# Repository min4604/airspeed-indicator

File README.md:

## Airspeeds system
Can use PC read real time data.

Schematic design end.

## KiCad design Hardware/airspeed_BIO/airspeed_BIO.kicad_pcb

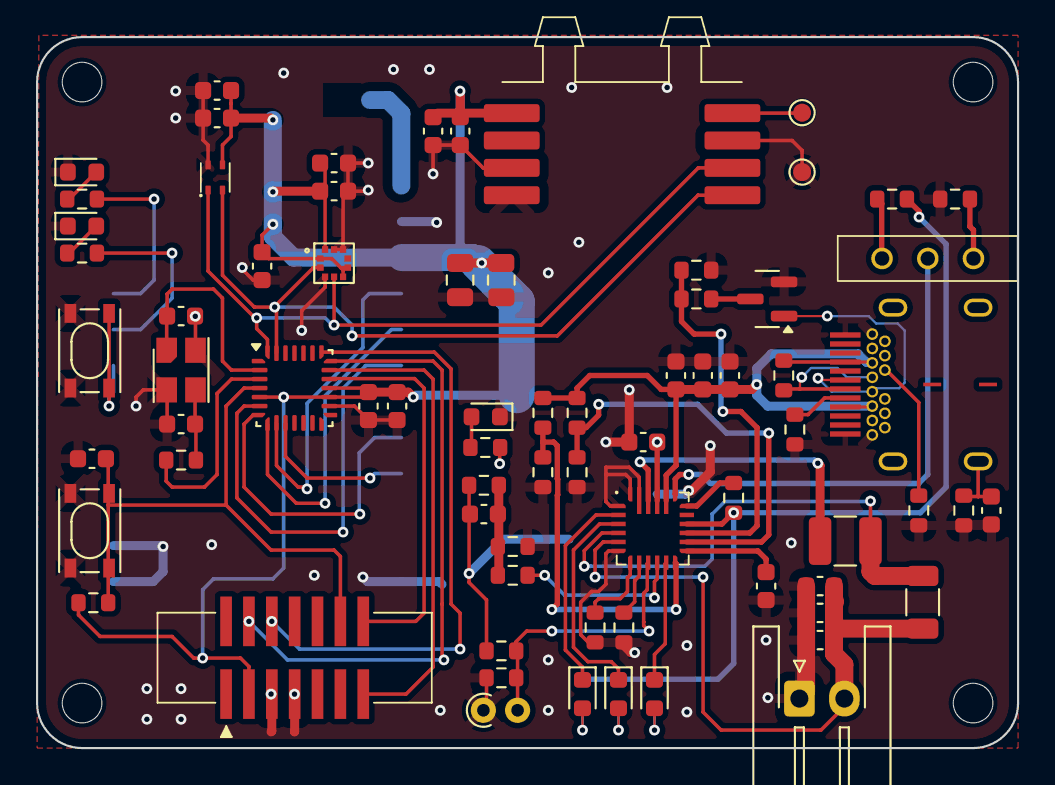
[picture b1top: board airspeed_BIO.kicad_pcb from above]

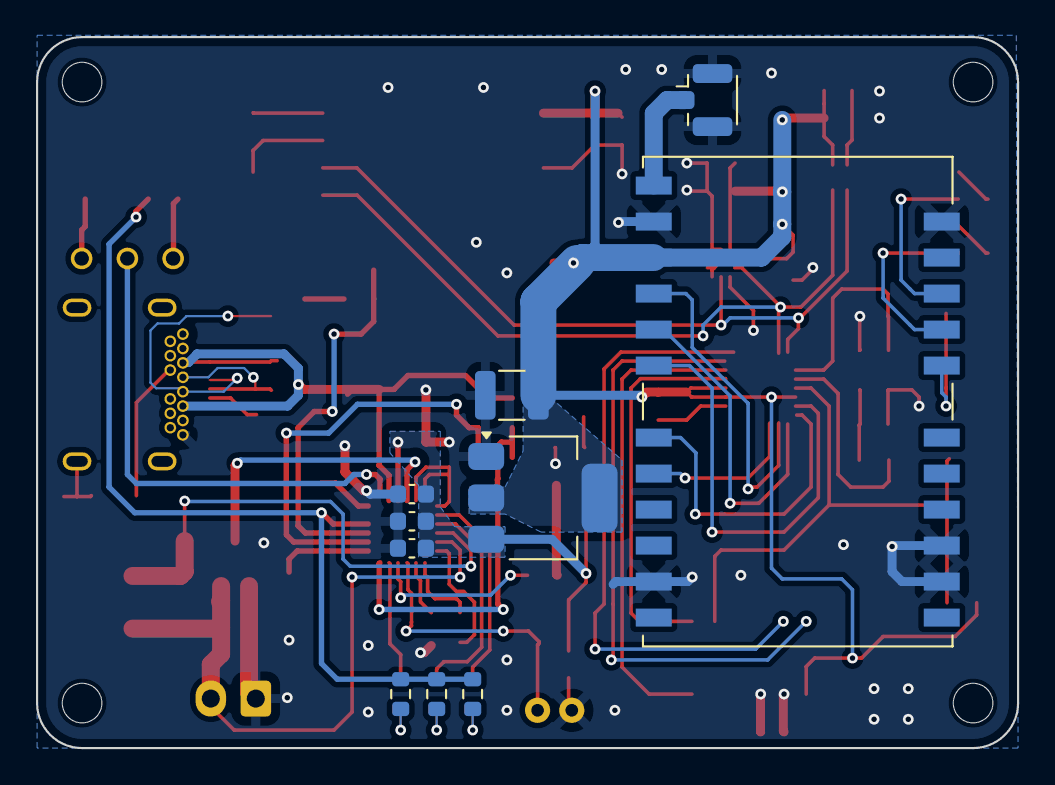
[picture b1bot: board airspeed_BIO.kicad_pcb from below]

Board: 2 copper layers, 54.5 x 39.5 mm, 87 parts (10 on the bottom side), 56 nets.

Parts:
C1, C9, C12: 22uF; C_0603_1608Metric
C2, C3, C4, C7, C8, C10, C11: 10uF; C_0603_1608Metric
C5: 120pF; C_0603_1608Metric
C6: 100nF; C_0603_1608Metric
C13: 4.7u_50V_we; C_1210_3225Metric
C14: 4.7n; C_0603_1608Metric
C15, C16, C18, C25: 4.7u; C_0603_1608Metric
C17, C19, C20, C21, C26: 0.1u; C_0603_1608Metric
C22, C23: 13p; C_0603_1608Metric
C24: 1u; C_0603_1608Metric
C27, C28: 47u; C_0805_2012Metric
D1: YLED; LED_0603_1608Metric
D2: BLED; LED_0603_1608Metric
D3: GLED; LED_0603_1608Metric
H1, H2, H3, H4: MountingHole; MountingHole_2.2mm_M2
J1: USB_C_Receptacle_USB2.0_16P; USB_C_Receptacle_WE_632723300011_hand
J2: LOG_DEBUG; 62731420621
J3: BATT; JST_XH_S2B-XH-A-1_1x02_P2.50mm_Horizontal
J4: RF; U.FL_Hirose_U.FL-R-SMT-1_Vertical
L1: 2.2uH; L_1210_3225Metric
Q1: 2N7002; SOT-23
R1, R2, R3: 5.1K; R_0603_1608Metric
R4: 45.3K; R_0603_1608Metric
R5: 23.7K; R_0603_1608Metric
R6: 15K; R_0603_1608Metric
R7, R24, R25: 2.1K; R_0603_1608Metric
R8: 90.9K; R_0603_1608Metric
R9, R26: 0; R_0603_1608Metric
R10: 31.6K; R_0603_1608Metric
R11, R14, R16: 10K; R_0603_1608Metric
R12: 57.6K; R_0603_1608Metric
R13: 120K; R_0603_1608Metric
R15: 20m; R_1206_3216Metric
R17: 845; R_0603_1608Metric
R18: 1.2K; R_0603_1608Metric
R19, R20: 2.7K; R_0603_1608Metric
R21: 1M; R_0603_1608Metric
R22, R23: 5.1k; R_0603_1608Metric
R27: 10k; R_0603_1608Metric
R28: 287; R_0603_1608Metric
R29: 374; R_0603_1608Metric
RLED1: 3.3V; LED_0603_1608Metric
RLED2: RX; LED_0603_1608Metric
SW1: SW_SPDT; switch_450301014042
SW2, SW3: 434123025826
TH1: 10K; R_Axial_DIN0204_L3.6mm_D1.6mm_P1.90mm_Vertical
TP1: GND; TestPoint_Pad_D1.0mm
TP2: Pressure Vout; TestPoint_Pad_D1.0mm
U1: MP2637GR-P; MP2637(QFN-24-4x4mm)
U2: LDL1117S33R; SOT-223-3_TabPin2
U3: 2511020213301
U4: 2513130810102; 2513130810102_hand
U5: 2525020210002
U6: STM32F042G6Ux; QFN-28_4x4mm_P0.5mm
U7: 2607011111000
Y1: 830108313809; WE-CFPX-180
YLED1: TX; LED_0603_1608Metric

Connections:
+3V3: C13.1, C15.1, C16.1, C17.1, C18.1, C19.1, C20.1, C21.1, C25.1, C26.1, C27.1, C28.1, J2.3, R20.2, R27.2, U2.2 (Vout), U3.1 (VDD_IO), U3.5 (SAO), U3.6 (CS), U3.10 (VDD), U4.5 (VDD), U5.3 (VDD), U6.5 (VDDA), U6.17 (VDD), U6.18 (VDDIO2), U7.3 (VCC)
+5V: C4.1, C5.1, C7.1, C8.1, C9.1, R10.1, R16.2, U1.21 (SYS), U2.3 (VIN)
/MCU/I2C1.SCL: U3.2 (SCL), U4.1 (SCL), U5.2 (SCL), U6.27 (PB6)
/MCU/I2C1.SDA: U3.4 (SDA), U4.2 (SDA), U5.1 (SDA), U6.28 (PB7)
/MCU/NRST: C24.1, J2.12, R27.1, SW2.3, SW2.4, U6.4 (NRST)
/MCU/RCC_OSC_IN: C22.1, U6.2 (PF0), Y1.1
/MCU/RCC_OSC_OUT: R26.2, U6.3 (PF1)
/MCU/SYS.SWCLK: J2.6, U6.22 (PA14)
/MCU/SYS.SWDIO: J2.4, U6.21 (PA13)
/MCU/USART1.RX: J2.13, U6.20 (PA10/PA12)
/MCU/USART1.TX: J2.14, U6.19 (PA9/PA11)
/MCU/USART2.CTS: U6.6 (PA0), U7.6 (~RTS)
/MCU/USART2.RTS: U6.7 (PA1), U7.7 (~CTS)
/MCU/USART2.RX: U6.9 (PA3), U7.4 (UTXD)
/MCU/USART2.TX: U6.8 (PA2), U7.5 (URXD)
/MCU/~DATA_IND: U6.10 (PA4), U7.8 (~DATA_IND)
/connector/BATT: C10.1, C11.1, C12.1, J3.2, R15.2, U1.5 (BATT)
/connector/EN_power: SW1.2 (B), U1.19 (MODE)
/connector/USB.D+: J1.A6 (D+), J1.B6 (D+), R1.1
/connector/USB.D-: J1.A7 (D-), J1.B7 (D-), Q1.1 (G)
/connector/USB.VBUS: C1.1, C2.1, C3.1, J1.A4 (VBUS), J1.A9 (VBUS), J1.B4 (VBUS), J1.B9 (VBUS), R1.2, R5.2, R6.2, U1.20 (VIN)
/power/NTC: R14.2, R16.1, TH1.2, U1.9 (NTC)
/power/VCCpm: R7.2, R17.2, R18.2, R19.2, R24.1, U1.16 (VCC)
/radio/RST: SW3.3, SW3.4, U7.19 (~RESET)
GND: C1.2, C2.2, C3.2, C4.2, C6.2, C7.2, C8.2, C9.2, C10.2, C11.2, C12.2, C13.2, C14.2, C15.2, C16.2, C17.2, C18.2, C19.2, C20.2, C21.2, C22.2, C23.2, C24.2, C25.2, C26.2, C27.2, C28.2, J1.A1 (GND), J1.A12 (GND), J1.B1 (GND), J1.B12 (GND), J2.5, J2.7, J3.1, J4.2 (Ext), Q1.2 (S), R2.1, R3.1, R8.1, R11.2, R12.2, R13.2, R14.1, R21.2, R22.1, R23.1, R25.2, RLED1.1 (K), RLED2.1 (K), SW2.1, SW2.2, SW3.1, SW3.2, TH1.1, TP1.1, U1.1 (PGND), U1.6 (AGND), U1.23 (PGND), U1.24 (PGND), U2.1 (GND), U3.3 (RSVD), U3.8 (GND), U3.9 (GND), U4.3 (GND), U4.7 (RSVD), U4.8 (RSVD), U5.4 (VSS), U6.16 (VSSA), U7.2 (GND), U7.11 (~DATA_REQ), U7.14 (TRX_DISABLE), U7.15 (~CONFIG), U7.23 (GND), Y1.2, Y1.4, YLED1.1 (K)
unnamed: C5.2, R9.1, R10.2, R11.1
unnamed: C23.1, R26.1, Y1.3
unnamed: D1.2 (A), R17.1
unnamed: D1.1 (K), U1.2 (~CHG)
unnamed: D2.2 (A), R18.1
unnamed: D2.1 (K), U1.11 (~ACOK)
unnamed: D3.2 (A), R19.1
unnamed: D3.1 (K), U1.3 (~BOOST)
unnamed: J1.A5 (CC1), R23.2
unnamed: J1.B5 (CC2), R22.2
unnamed: C14.1, J1.S1 (SHIELD), R21.1
unnamed: J4.1 (In), U7.1 (ANT)
unnamed: Q1.3 (D), R4.1
unnamed: R20.1, RLED1.2 (A)
unnamed: R28.2, RLED2.2 (A)
unnamed: R24.2, SW1.1 (A)
unnamed: R25.1, SW1.3 (C)
unnamed: L1.2, R15.1, U1.4 (CSP)
unnamed: R7.1, U1.18 (EN)
unnamed: R9.2, U1.10 (FB)
unnamed: R4.2, R8.2, U1.15 (ILIM)
unnamed: R13.1, U1.8 (ISET)
unnamed: R12.1, U1.7 (OLIM)
unnamed: R2.2, R5.1, U1.14 (PWIN)
unnamed: R3.2, R6.1, U1.12 (REG)
unnamed: L1.1, U1.22 (SW)
unnamed: C6.1, U1.13 (TMR)
unnamed: TP2.1, U4.4 (VOUT)
unnamed: R28.1, U7.21 (RX_INDICATE)
unnamed: R29.1, U7.20 (TX_INDICATE)
unnamed: R29.2, YLED1.2 (A)

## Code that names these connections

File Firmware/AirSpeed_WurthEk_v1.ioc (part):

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Mcu.Name=STM32F042G(4-6)Ux
Mcu.Package=UFQFPN28
Mcu.UserName=STM32F042G6Ux
PA10.Mode=Asynchronous
PA10.Signal=USART1_RX
PA13.Mode=Serial_Wire
PA13.Signal=SYS_SWDIO
PA14.Mode=Serial_Wire
PA14.Signal=SYS_SWCLK
PA2.Mode=Asynchronous
PA2.Signal=USART2_TX
PA3.Mode=Asynchronous
PA3.Signal=USART2_RX
PA9.Mode=Asynchronous
PA9.Signal=USART1_TX
PB6.GPIOParameters=GPIO_Pu
PB6.GPIO_Pu=GPIO_PULLUP
PB6.Mode=I2C
PB6.Signal=I2C1_SCL
PB7.GPIOParameters=GPIO_Pu
PB7.GPIO_Pu=GPIO_PULLUP
PB7.Mode=I2C
PB7.Signal=I2C1_SDA
RCC.SYSCLKFreq_VALUE=48000000
RCC.SYSCLKSource=RCC_SYSCLKSOURCE_HSI48
board=custom

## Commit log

2025-07-11 add README
2025-07-11 first set .gitignore
2025-07-11 fix readme
2025-07-11 fix gitignore
2025-07-11 start PCB design
2025-07-13 Power management system save
2025-07-14 power end didn't set I limit
2025-07-15 add mcu audio
2025-07-18 set Ilimit and set footprint
2025-07-19 layout and fix Schematic
2025-07-19 readme updata
2025-07-30 layoyt end
2025-07-30 add release
2025-08-04 fix ibom
2025-09-08 fix pcb
2025-10-29 no message
2025-10-29 getdataOK
2025-10-29 add software
2025-10-30 UI add new data and save
2025-10-30 docs: 初始框架並新增README.md
    調整項目：新增分支並初始化框架，調整sw使用ipc作為核心通訊協定，使未來擴充muti-channel更為方便
2025-10-31 feat: 新增基礎框架與啟動器
    調整項目:
    1. `serial_reader.py`, `analyze.py`為子程式負責細項工作
    2. `launcher.py`負責啟動監測與關閉子進程
    3. utils 避免重複造輪子
    4. uart_format.json 為未來格式統一擴展
    tkx
2025-11-02 feat: 完成 IPC PUB 與 SUB 功能測試，並新增Python 模板，請協助後續功能完善與驗證
    調整項目:
    1. `serial_reader.py` 發布假訊號與 `analyze.py` 接受(請合併pyserial code 與測試)
    2. 完成 RPI4 4G 板上測試且 CPU load 不超過 5%
    3. 補充 `README.md`
    4. 調整 `utils` 內套件不使用 log 系統 (path 相依衝突)
    5. `launcher.py` 調整使用 KeyboardInterrupt 關閉子進程，研究後續整合console系統
2025-11-05 feat: 新增 `serial_reader.py` testbench 誘騙封包
    調整項目:
    1. 新增 `fake_tty_trans` 工具，使用封包格式 json 檔回傳假訊號
    tkx
2025-11-07 fix: 修正bug並新增csv轉換器
    調整項目
    - `fix #3`
    - `fix #4`
    - 新增 `uart_format_conv.py` 與 csv 模板
    tkx
2026-03-23 add CAN
